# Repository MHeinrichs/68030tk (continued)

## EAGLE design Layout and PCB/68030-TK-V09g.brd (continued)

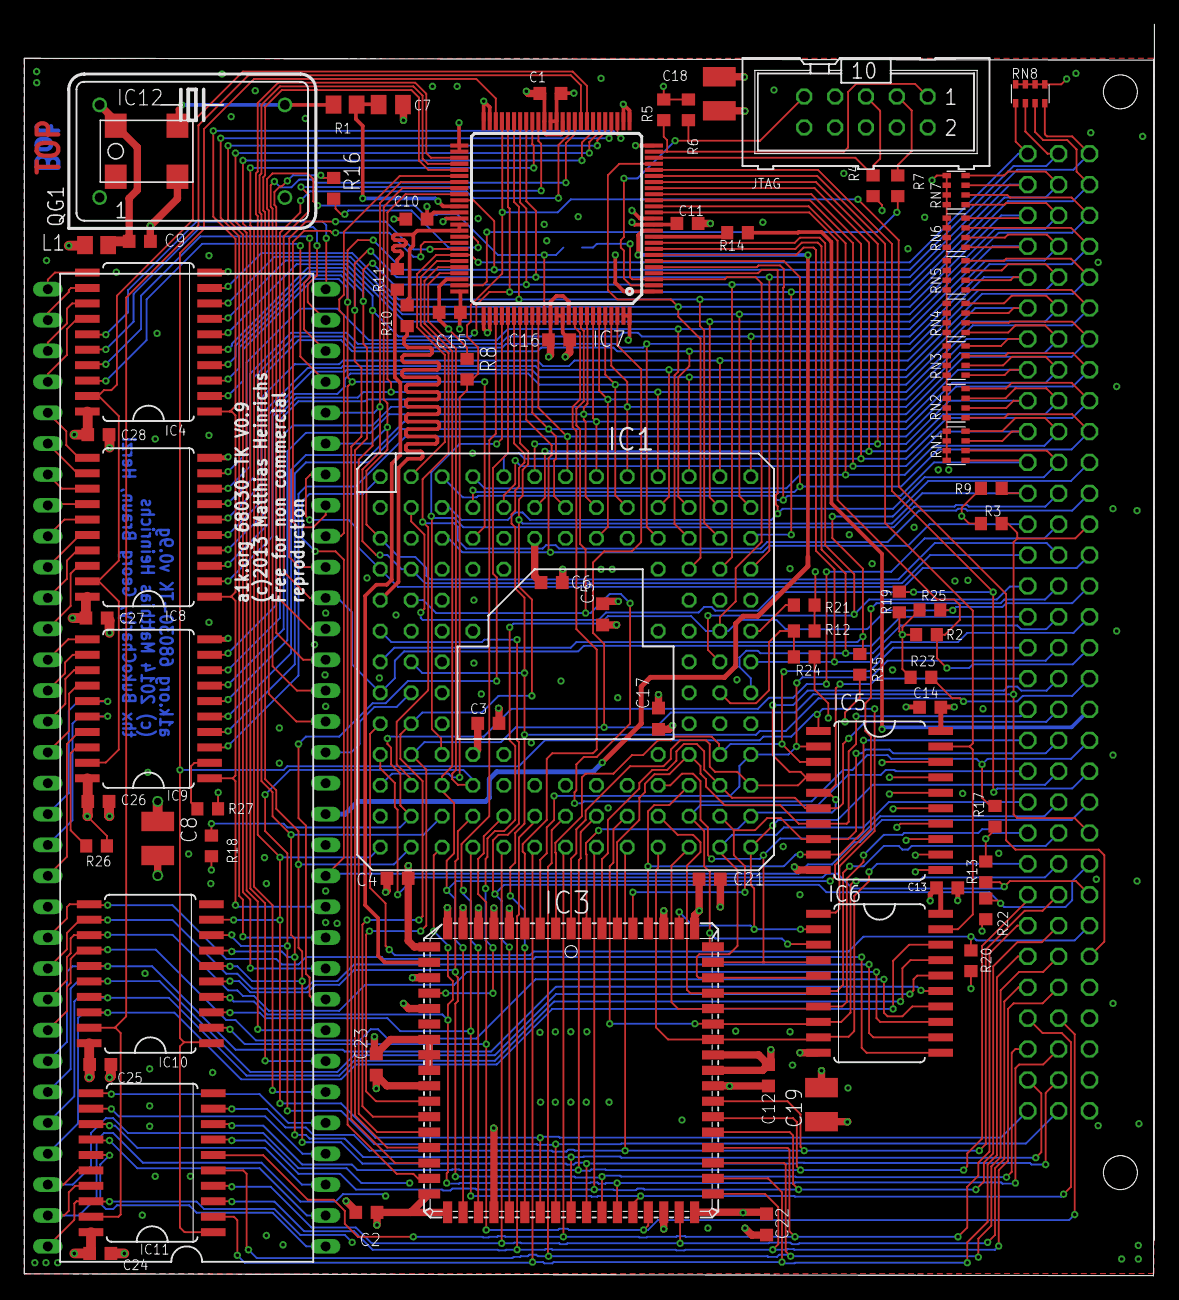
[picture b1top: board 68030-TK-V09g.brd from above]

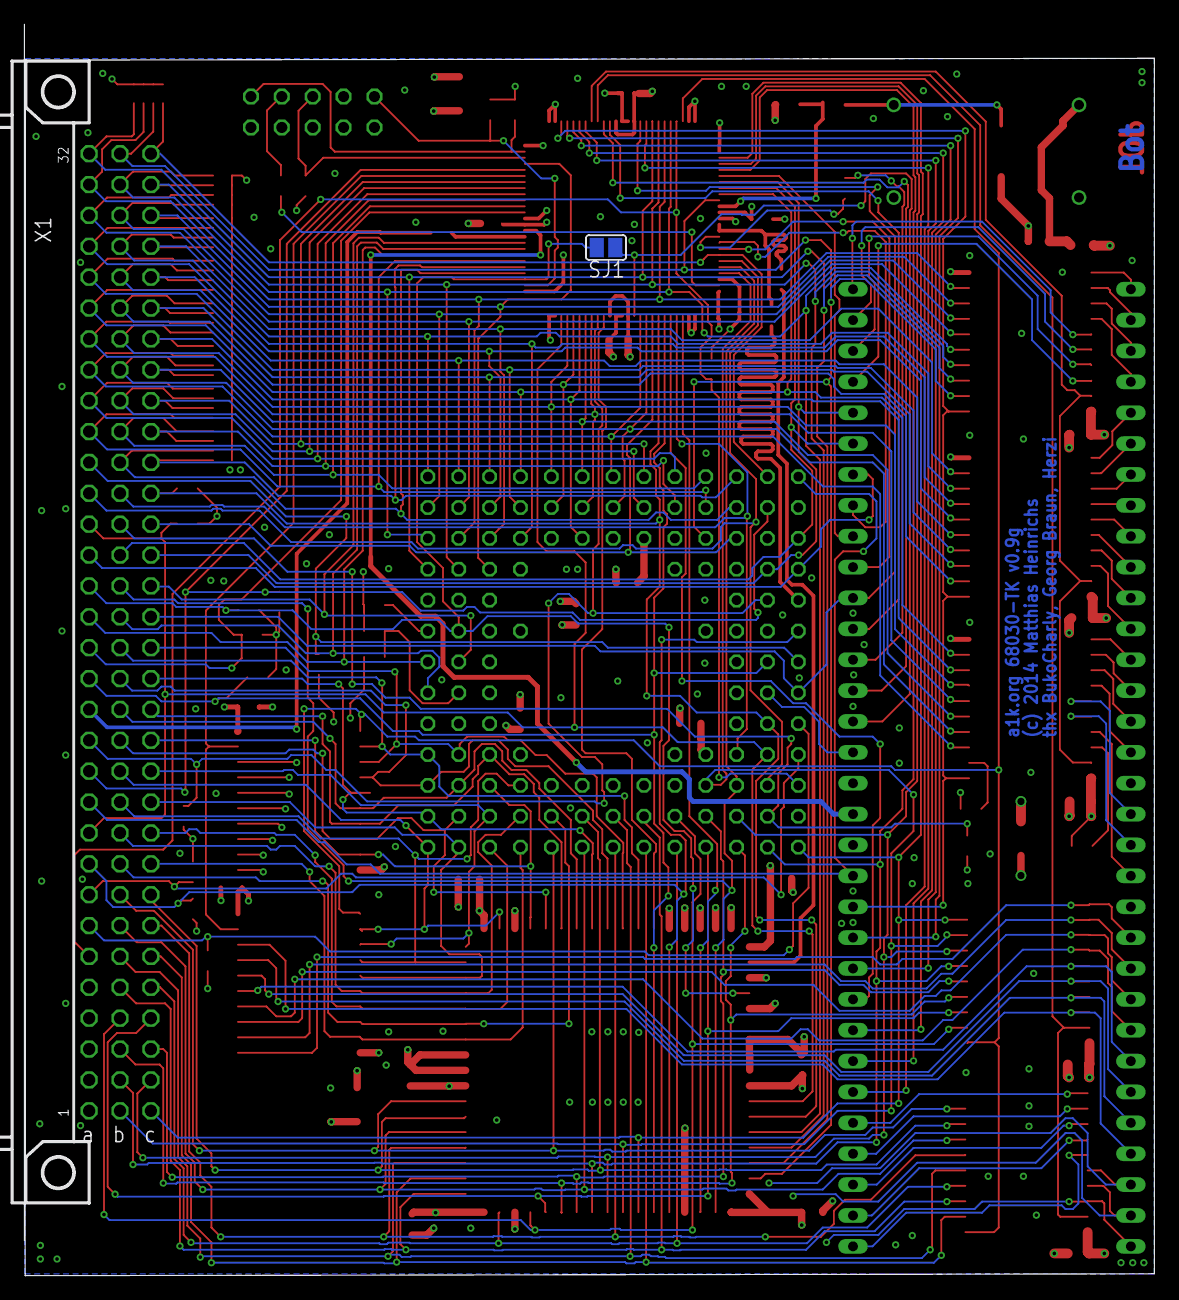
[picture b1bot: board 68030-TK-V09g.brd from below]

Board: 4 copper layers, 93.0 x 102.9 mm, 79 parts (2 on the bottom side), 170 nets.

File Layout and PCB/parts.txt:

Partlist

Exported from 68030-TK-V09d.brd at 16.07.2014 09:03:11

EAGLE Version 6.6.0 Copyright (c) 1988-2014 CadSoft

Assembly variant: 

Part     Value          Package  Library            Position (mil)        Orientation

C1       100nF          C0603K   rcl                (1704 3823)           R0
C2       100nF          C0603K   rcl                (1108 199)            R180
C3       100nF          C0603K   rcl                (1503 1783)           R0
C4       100nF          C0603K   rcl                (1209 1281)           R180
C5       100nF          C0603K   rcl                (1873 2136)           R90
C6       100nF          C0603K   rcl                (1708 2239)           R0
C7       n.b.           C0805K   rcl                (1187 3787)           R0
C8       10µF           C1210    rcl                (432 1410)            R270
C9       100nF          C0603K   rcl                (374 3344)            R0
C10      100nF          C0603K   rcl                (1270 3416)           R180
C11      100nF          C0603K   rcl                (2148 3402)           R0
C12      100nF          C0603K   rcl                (2410 643)            R270
C13      100nF          C0603K   rcl                (2989 1250)           R0
C14      100nF          C0603K   rcl                (2934 1835)           R180
C15      100nF          C0603K   rcl                (1378 3114)           R0
C16      100nF          C0603K   rcl                (1732 3025)           R0
C17      100nF          C0603K   rcl                (2054 1798)           R90
C18      10µF           C1210    rcl                (2251 3822)           R270
C19      10µF           C1210    rcl                (2582 548)            R90
C21      100nF          C0603K   rcl                (2220 1278)           R0
C22      100nF          C0603K   rcl                (2404 160)            R270
C23      100nF          C0603K   rcl                (1140 678)            R270
C24      100nF          C0603K   rcl                (246 66)              R0
C25      100nF          C0603K   rcl                (246 678)             R0
C26      100nF          C0603K   rcl                (240 1530)            R0
C27      100nF          C0603K   rcl                (234 2124)            R0
C28      100nF          C0603K   rcl                (240 2718)            R0
IC1                     MPGA128  micro-mc68000      (1753 1982)           R0
IC2                     DIL64    micro-mc68000      (526 1639)            R90
IC3                     PLCC68   micro-mc68000      (1771 659)            R0
IC4      74HCT245DW     SO20W    74xx-eu            (402 3018)            R90
IC5      74HCT245DW     SO20W    74xx-eu            (2770 1533)           R270
IC6      74HCT245DW     SO20W    74xx-eu            (2770 941)            R270
IC7                     TQFP100  amd-mach-Small-pad (1724 3418)           R180
IC8      74HCT245DW     SO20W    74xx-eu            (402 2418)            R90
IC9      74HCT245DW     SO20W    74xx-eu            (402 1830)            R90
IC10     74HCT245DW     SO20W    74xx-eu            (408 972)             R90
IC11     74HCT245DW     SO20W    74xx-eu            (414 360)             R90
L1       4.7            R0805    rcl                (234 3332)            R0
QG1      100MHz         DIL14S   crystal            (544 3636)            R0
R1       47             R0805    rcl                (1039 3787)           R0
R2       4,7k           R0603    rcl                (2922 2070)           R180
R3       4,7k           R0603    rcl                (3132 2430)           R0
R4       4,7k           R0603    rcl                (2749 3524)           R270
R5       4,7k           R0603    rcl                (2071 3770)           R90
R6       4,7k           R0603    rcl                (2151 3770)           R90
R7       47             R0603    rcl                (2829 3524)           R270
R8       4,7k           R0603    rcl                (1434 2930)           R270
R9       4,7k           R0603    rcl                (3132 2544)           R0
R10      68             R0603    rcl                (1240 3103)           R270
R11      68             R0603    rcl                (1208 3221)           R270
R12      4,7k           R0603    rcl                (2526 2082)           R0
R13      4,7k           R0603    rcl                (3114 1302)           R90
R14      68             R0603    rcl                (2310 3372)           R180
R15      4,7k           R0603    rcl                (2706 1974)           R270
R16      47             R0603    rcl                (1002 3516)           R90
R17      4,7k           R0603    rcl                (3144 1482)           R90
R18      4,7k           R0603    rcl                (606 1386)            R90
R19      4,7k           R0603    rcl                (2834 2176)           R90
R20      4,7k           R0603    rcl                (3066 1014)           R270
R21      4,7k           R0603    rcl                (2526 2166)           R0
R22      4,7k           R0603    rcl                (3114 1182)           R90
R23      4,7k           R0603    rcl                (2904 1932)           R0
R24      4,7k           R0603    rcl                (2526 1998)           R0
RN1      4,7k           EXBV8V   resistor-dil       (3120 2682)           R90
RN2      4,7k           EXBV8V   resistor-dil       (3120 2820)           R90
RN3      4,7k           EXBV8V   resistor-dil       (3120 2958)           R90
RN4      4,7k           EXBV8V   resistor-dil       (3120 3096)           R90
RN5      4,7k           EXBV8V   resistor-dil       (3120 3234)           R90
RN6      4,7k           EXBV8V   resistor-dil       (3120 3372)           R90
RN7      4,7k           EXBV8V   resistor-dil       (3120 3510)           R90
RN8      4,7k           EXBV8V   resistor-dil       (3258 3738)           R0
SV1                     ML10     con-harting-ml     (2726 3763)           R180
X1       FABC96R        FABC96R  con-vg             (3550 2078)           MR180

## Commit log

2014-05-15 Initial push
    First VErsion after I decided to use version controll ;)
2014-05-15 Working!
2014-05-15 Before clean up
2014-05-15 Cleaned up version
    This version is the base for all future experiments.
2014-05-16 Fixed external interface flaws
2014-05-16 Copyright-notice added
2014-05-19 50Mhz Clock working
2014-05-22 sync
2014-05-24 better amiga timing
2014-05-24 33MHz @100MHz basis working
2014-05-24 Bug in DMA
2014-05-24 DMA working on Amiga-side
2014-05-24 DMA-TK-Side first non working version
2014-05-25 DMA-(potentially) working version but only 25Mhz
2014-05-25 timing enhanced?
2014-05-28 dma-working and prework for turbo side
2014-05-29 minor clean up
2014-06-01 New PCB and start for RW-Signal-Optimization
2014-06-07 RW-Fixed
2014-06-09 PE/NE-Sync started
2014-06-09 Caching for mem enabled
2014-06-09 Cache-Disable-Option on PCB
2014-06-15 Some Changes regarding CIIN and Timing
2014-06-17 credits added
2014-06-22 Chasing the WingCommander Bug
2014-06-22 one file missing
2014-06-23 trhs
2014-07-18 New file for PCB Rev 0.9d
2014-08-09 Wing Commander works but generally instable?!
2014-08-09 Chasing the instability
2014-08-09 Stable! (up to now ;) )
2014-08-12 Update - minor changes
2014-08-12 Stuck at 25MHz
2014-08-26 Working @50MHz
2014-09-16 DMA-Started
2014-10-03 More stability in constraints
2014-10-04 Tristating bus drivers
2014-10-07 Tristating Data was a bad idea
2014-10-10 There is a bug somewhere!!!
2014-10-16 Cleaned up
2015-01-12 DMA Working
2015-02-01 DMA Improved for A2000
2015-02-03 DMA Improved and Reset pulled up
2015-02-03 DMA working for GVP
2015-02-13 DMA Back to A500: Working
2015-02-19 Adress bus on permanently
    The adress bus is now on permanently. This is neccessary because some
    GARY-Adapters decode the address before AS
2015-03-15 Reset-Problem solved
    The AMiga was not able to recover from a reste, because the e-clock was
    not generated properly during reste.
2015-03-28 Sources for GBA-TK060
2015-06-26 MIsc. Update
2015-07-18 some erratic tries
2015-09-24 DMA-Bug fixed
    When BGACK gets deasserted, the DMA-Statemachine has to wait for AS_000
    to deassert too!
2015-10-10 Reset-Circuit has less delay
2016-01-24 Cleaned up a bit
2016-01-25 50Mhz version
2016-01-28 Some jed-files generated
2016-05-20 added a alternative for the oscillator
2016-06-02 Values corrected
2016-08-18 Clean up
2016-08-18 Clarified some thing Timing can be adjusted with constants
2016-08-18 Horray! No Sync of Pos and Neg edges needed anymore!
2016-08-24 Working at 254Mhz in CDTV!
2016-08-25 Cleaned up and the preempting DSACK is unneccessary?!?
2016-09-15 Cleaned up BRD-Files
2016-10-06 Improved speed on amiga cycles
2016-10-06 recompiled
2016-10-16 timing timing timnig ... when will it end?
2016-10-26 Updated some JEDs
2016-11-30 Better timing & Resetfix
2016-12-29 resetfix + pdfs
2017-01-04 Resetfix in PCB
2017-12-30 dma improved
2018-01-11 DMA-Fix: Assume $E8-EF 16 bit wide!
2019-08-28 Moved to gitlab
2019-08-28 Removed files and added link in readme
2019-08-28 Removed readme.txt
2019-08-28 fixed README.md
